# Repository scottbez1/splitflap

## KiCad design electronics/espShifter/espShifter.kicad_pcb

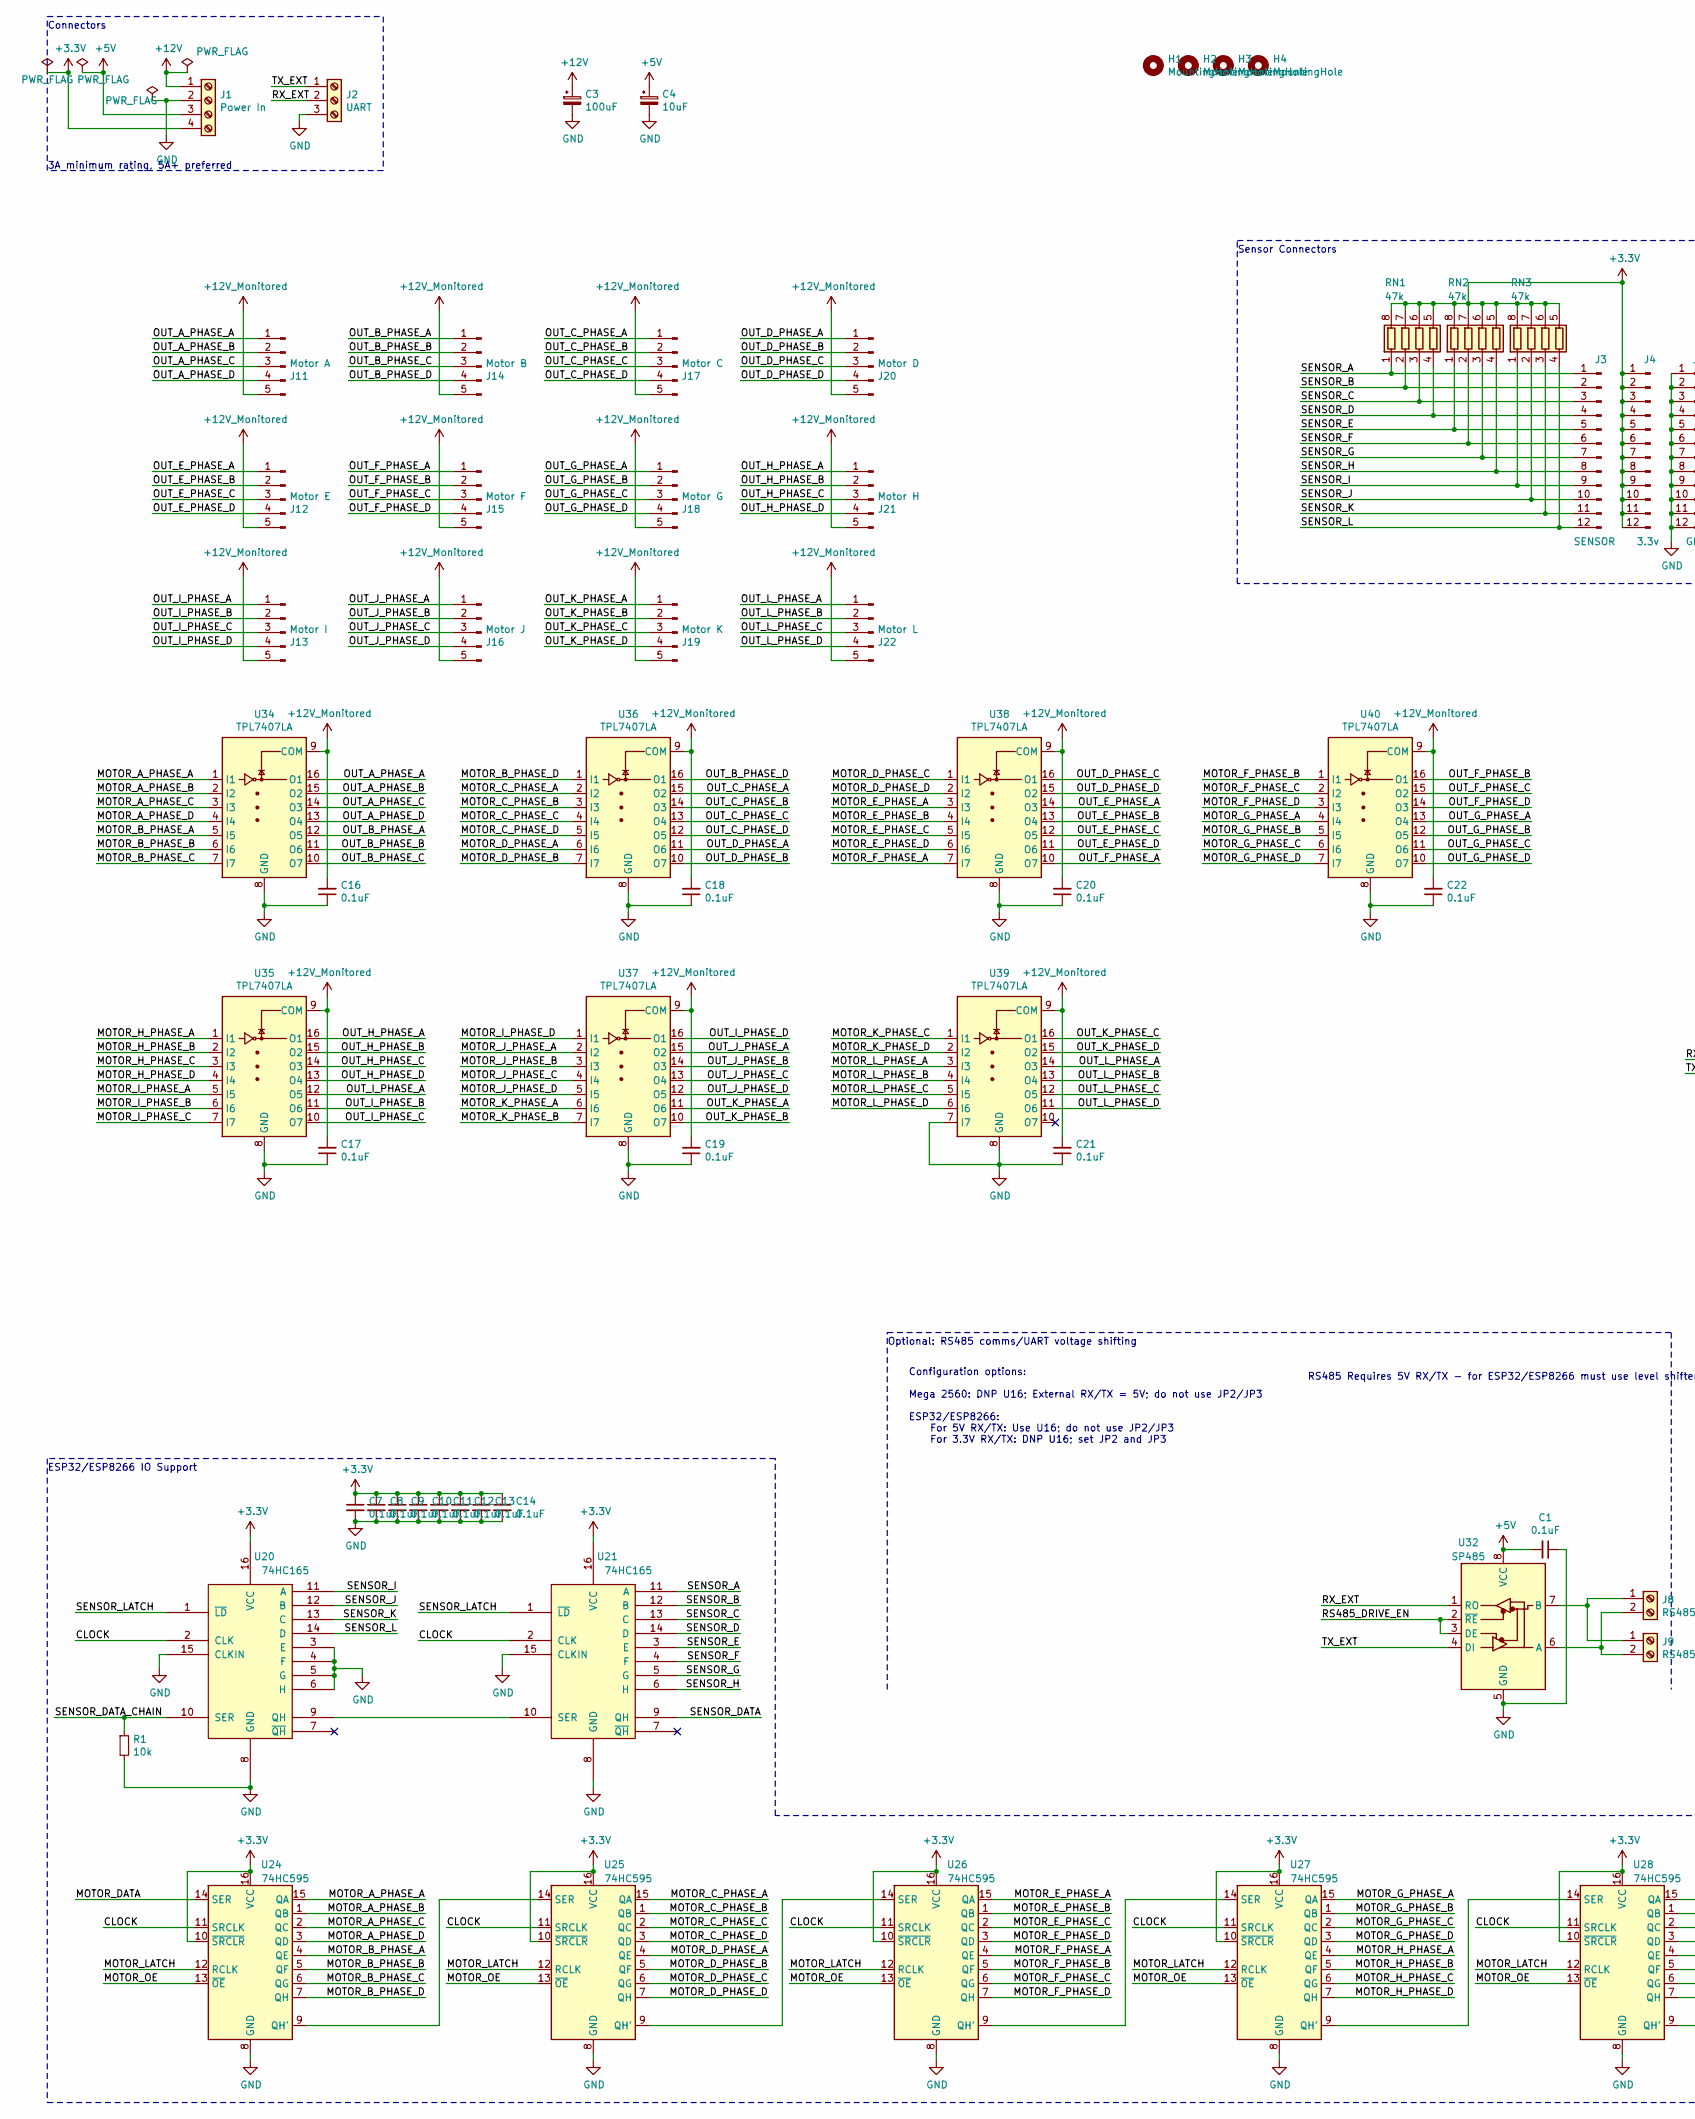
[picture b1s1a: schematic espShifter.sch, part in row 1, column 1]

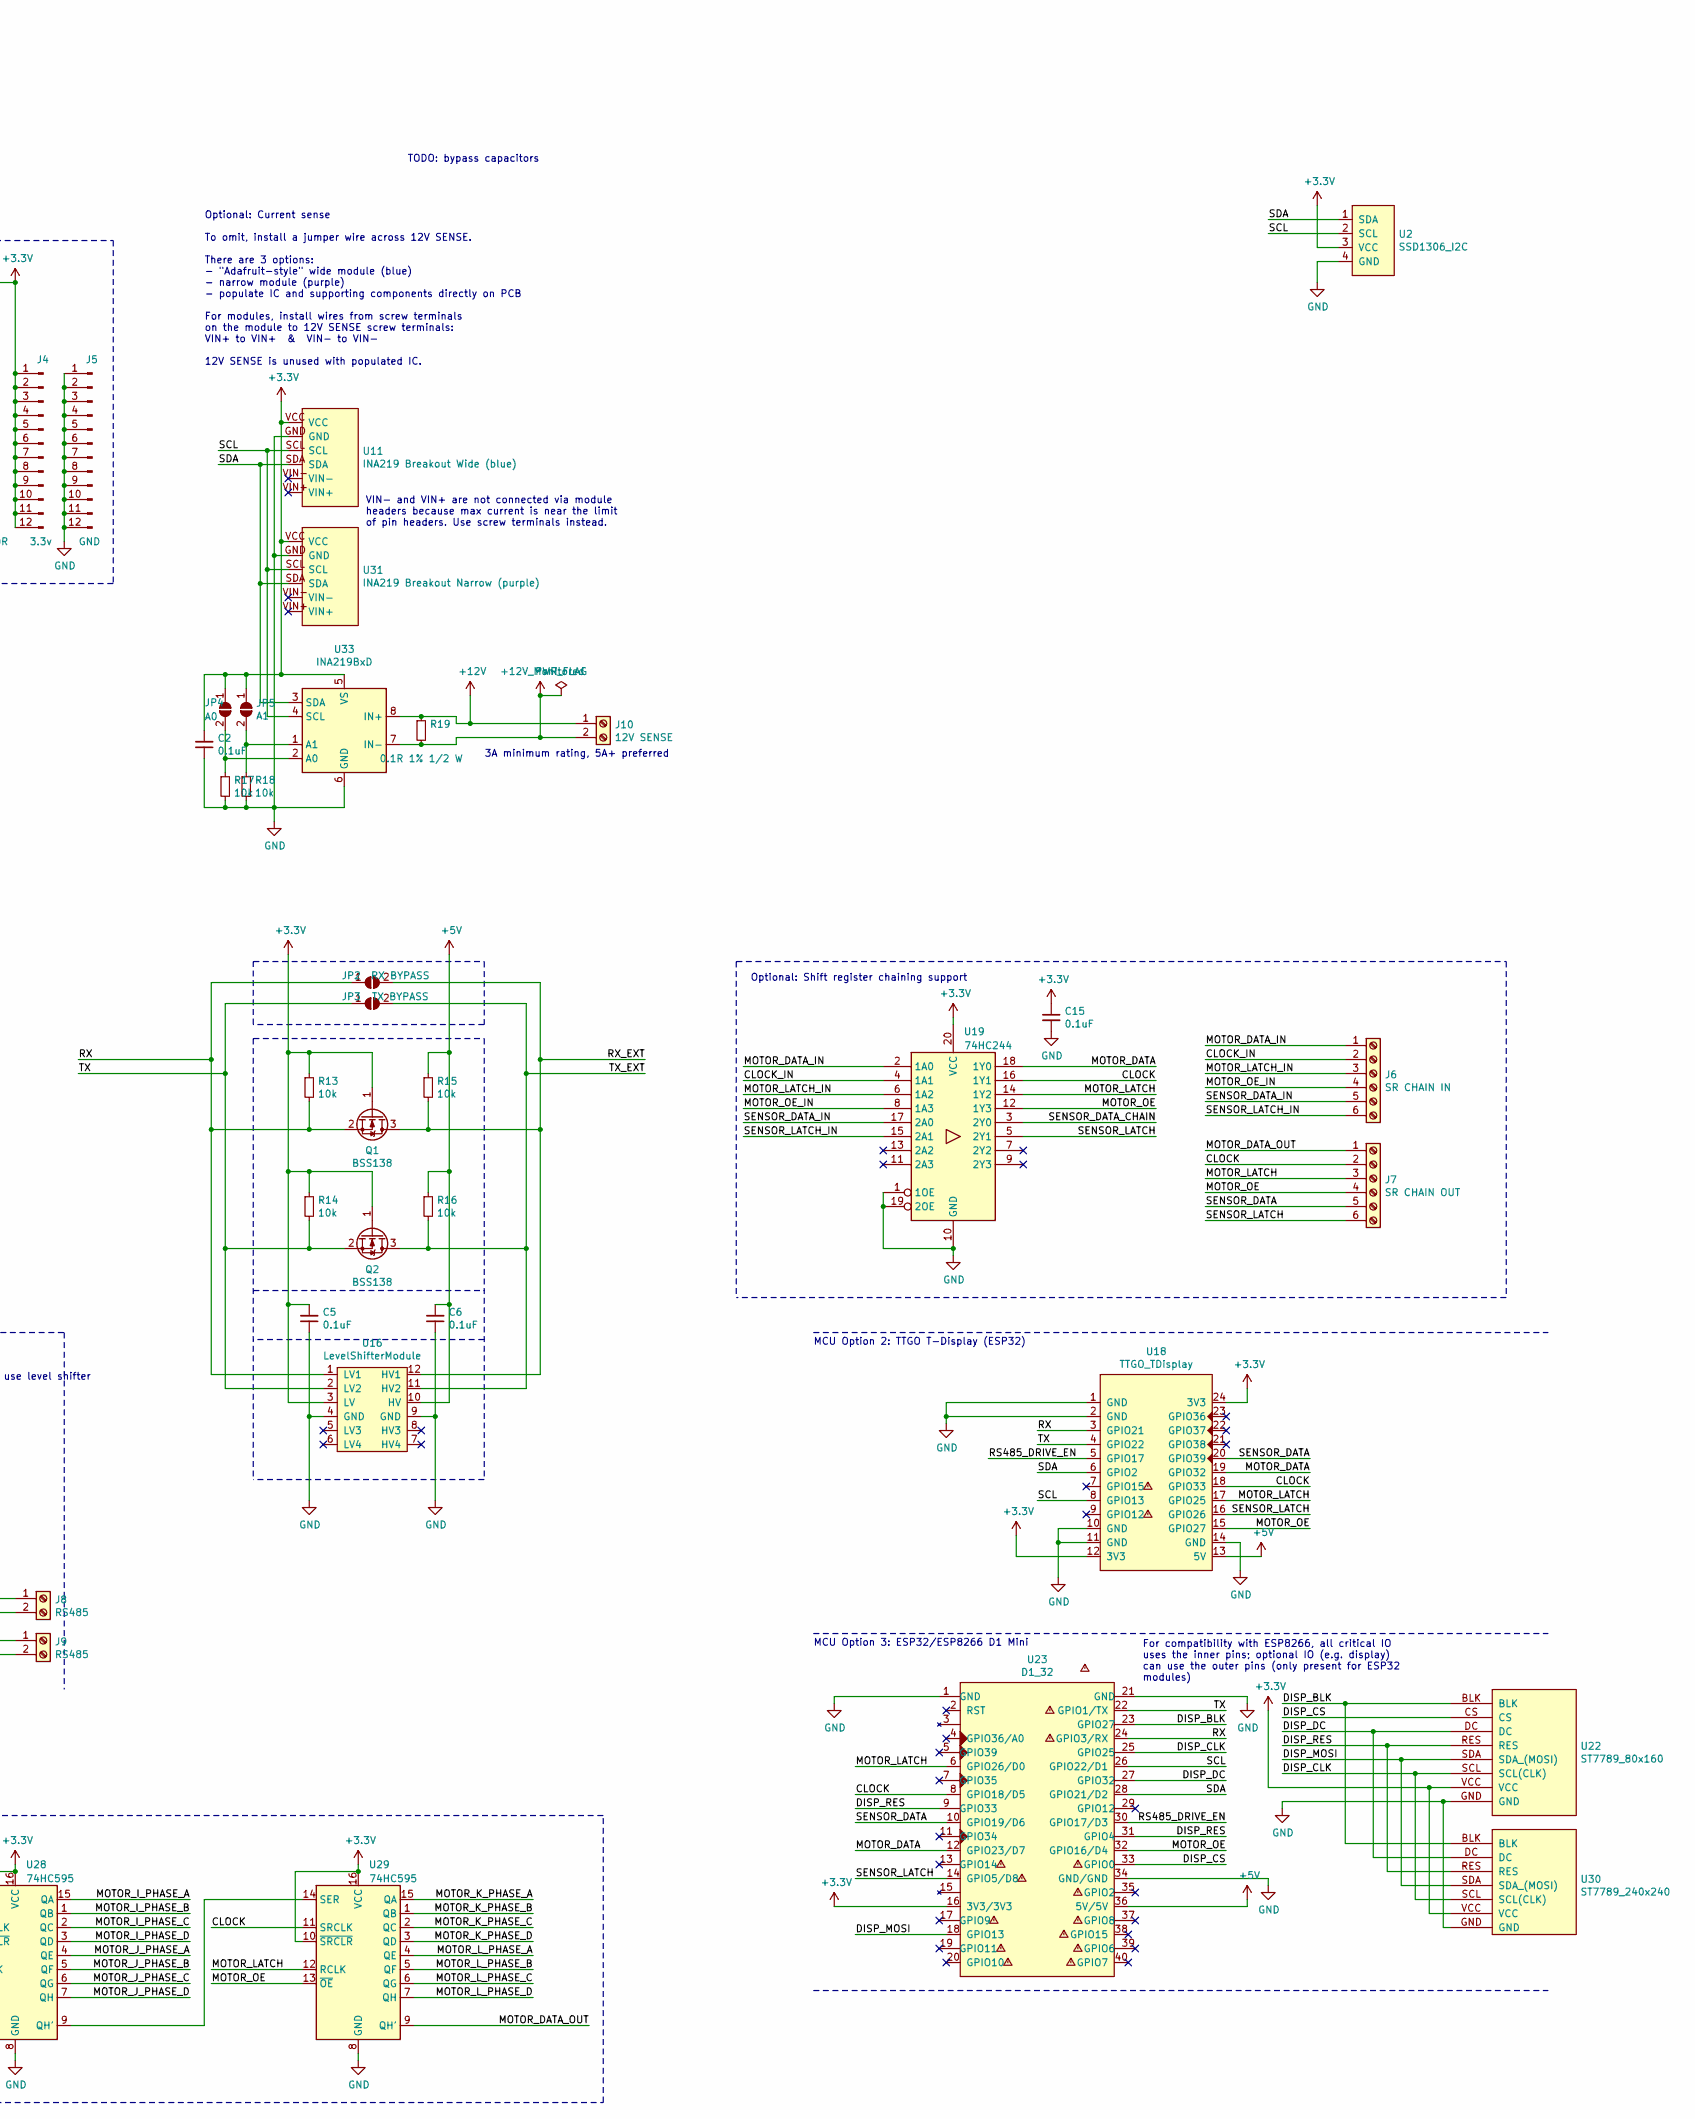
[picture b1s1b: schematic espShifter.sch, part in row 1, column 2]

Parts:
C1, C2, C5, C6, C7, C8, C9, C10, C11, C12, C13, C14, C15, C16, C17, C18, C19, C20, C21, C22: 0.1uF; C_0805_2012Metric
C3: 100uF; CP_Elec_8x10.5
C4: 10uF; CP_Elec_4x5.4
H1, H2, H3, H4: MountingHole; MountingHole_4.3mm_M4_ISO7380_Pad
J1: Power In; TerminalBlock_bornier-4_P5.08mm
J2: UART; TerminalBlock_bornier-3_P5.08mm
J3: SENSOR; PinHeader_1x12_P2.54mm_Vertical
J4: 3.3v; PinHeader_1x12_P2.54mm_Vertical
J5: GND; PinHeader_1x12_P2.54mm_Vertical
J6: SR CHAIN IN; PinSocket_1x06_P2.54mm_Vertical
J7: SR CHAIN OUT; PinSocket_1x06_P2.54mm_Vertical
J8, J9: RS485; TerminalBlock_bornier-2_P5.08mm
J10: 12V SENSE; TerminalBlock_bornier-2_P5.08mm
J11: Motor A; JST_XH_2-5mm_5pin
J12: Motor E; JST_XH_2-5mm_5pin
J13: Motor I; JST_XH_2-5mm_5pin
J14: Motor B; JST_XH_2-5mm_5pin
J15: Motor F; JST_XH_2-5mm_5pin
J16: Motor J; JST_XH_2-5mm_5pin
J17: Motor C; JST_XH_2-5mm_5pin
J18: Motor G; JST_XH_2-5mm_5pin
J19: Motor K; JST_XH_2-5mm_5pin
J20: Motor D; JST_XH_2-5mm_5pin
J21: Motor H; JST_XH_2-5mm_5pin
J22: Motor L; JST_XH_2-5mm_5pin
JP2: RX BYPASS; SolderJumper-2_P1.3mm_Open_TrianglePad1.0x1.5mm
JP3: TX BYPASS; SolderJumper-2_P1.3mm_Open_TrianglePad1.0x1.5mm
JP4: A0; SolderJumper-2_P1.3mm_Open_TrianglePad1.0x1.5mm
JP5: A1; SolderJumper-2_P1.3mm_Open_TrianglePad1.0x1.5mm
Q1, Q2: BSS138; SOT-23
R1, R13, R14, R15, R16, R17, R18: 10k; R_0805_2012Metric
R19: 0.1R 1% 1/2 W; R_2512_6332Metric_Pad1.52x3.35mm_HandSolder
RN1, RN2, RN3: 47k; R_Cat16-4
U2: SSD1306_I2C; PinSocket_1x04_P2.54mm_Vertical
U11: INA219 Breakout Wide (blue); INA219_LARGE
U16: LevelShifterModule
U18: TTGO_TDisplay; T-DISPLAY
U19: 74HC244; TSSOP-20_4.4x6.5mm_P0.65mm
U20, U21: 74HC165; SOIC-16_3.9x9.9mm_P1.27mm
U22: ST7789_80x160
U23: D1_32
U24, U25, U26, U27, U28, U29: 74HC595; SOIC-16_3.9x9.9mm_P1.27mm
U30: ST7789_240x240
U31: INA219 Breakout Narrow (purple); INA219_SMALL
U32: SP485; SOIC-8_3.9x4.9mm_P1.27mm
U33: INA219BxD; SOIC-8_3.9x4.9mm_P1.27mm
U34, U35, U36, U37, U38, U39, U40: TPL7407LA; SOIC-16_3.9x9.9mm_P1.27mm

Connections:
+3V3: C2.2, C5.2, C7.1, C8.1, C9.1, C10.1, C11.1, C12.1, C13.1, C14.1, C15.1, J1.4, J4.1, J4.2, J4.3, J4.4, J4.5, J4.6, J4.7, J4.8, J4.9, J4.10, J4.11, J4.12, JP4.1 (A), JP5.1 (A), Q1.1 (G), Q2.1 (G), R13.1, R14.1, RN1.5 (R4.2), RN1.6 (R3.2), RN1.7 (R2.2), RN1.8 (R1.2), RN2.5 (R4.2), RN2.6 (R3.2), RN2.7 (R2.2), RN2.8 (R1.2), RN3.5 (R4.2), RN3.6 (R3.2), RN3.7 (R2.2), RN3.8 (R1.2), U2.3 (VCC), U11.VCC, U16.3 (LV), U18.12 (3V3), U18.24 (3V3), U19.20 (VCC), U20.16 (VCC), U21.16 (VCC), U22.VCC, U23.16 (3V3/3V3), U24.10 (~SRCLR), U24.16 (VCC), U25.10 (~SRCLR), U25.16 (VCC), U26.10 (~SRCLR), U26.16 (VCC), U27.10 (~SRCLR), U27.16 (VCC), U28.10 (~SRCLR), U28.16 (VCC), U29.10 (~SRCLR), U29.16 (VCC), U30.VCC, U31.VCC, U33.5 (VS)
+5V: C1.2, C4.1, C6.2, J1.3, R15.1, R16.1, U16.10 (HV), U18.13 (5V), U23.36 (5V/5V), U32.8 (VCC)
+12V: C3.1, J1.1, J10.1, R19.1, U33.8 (IN+)
+12V_Monitored: C16.2, C17.2, C18.2, C19.2, C20.2, C21.2, C22.2, J10.2, J11.5, J12.5, J13.5, J14.5, J15.5, J16.5, J17.5, J18.5, J19.5, J20.5, J21.5, J22.5, R19.2, U33.7 (IN-), U34.9 (COM), U35.9 (COM), U36.9 (COM), U37.9 (COM), U38.9 (COM), U39.9 (COM), U40.9 (COM)
/CLOCK: J7.2, U18.18 (GPIO33), U19.16 (1Y1), U20.2 (CLK), U21.2 (CLK), U23.8 (GPIO18/D5), U24.11 (SRCLK), U25.11 (SRCLK), U26.11 (SRCLK), U27.11 (SRCLK), U28.11 (SRCLK), U29.11 (SRCLK)
/CLOCK_IN: J6.2, U19.4 (1A1)
/DISP_BLK: U22.BLK, U23.23 (GPIO27), U30.BLK
/DISP_CLK: U22.SCL (SCL(CLK)), U23.25 (GPIO25), U30.SCL (SCL(CLK))
/DISP_CS: U22.CS, U23.33 (GPIO0)
/DISP_DC: U22.DC, U23.27 (GPIO32), U30.DC
/DISP_MOSI: U22.SDA (SDA_(MOSI)), U23.18 (GPIO13), U30.SDA (SDA_(MOSI))
/DISP_RES: U22.RES, U23.9 (GPIO33), U23.31 (GPIO4), U30.RES
/MOTOR_A_PHASE_A: U24.15 (QA), U34.1 (I1)
/MOTOR_A_PHASE_B: U24.1 (QB), U34.2 (I2)
/MOTOR_A_PHASE_C: U24.2 (QC), U34.3 (I3)
/MOTOR_A_PHASE_D: U24.3 (QD), U34.4 (I4)
/MOTOR_B_PHASE_A: U24.4 (QE), U34.5 (I5)
/MOTOR_B_PHASE_B: U24.5 (QF), U34.6 (I6)
/MOTOR_B_PHASE_C: U24.6 (QG), U34.7 (I7)
/MOTOR_B_PHASE_D: U24.7 (QH), U36.1 (I1)
/MOTOR_C_PHASE_A: U25.15 (QA), U36.2 (I2)
/MOTOR_C_PHASE_B: U25.1 (QB), U36.3 (I3)
/MOTOR_C_PHASE_C: U25.2 (QC), U36.4 (I4)
/MOTOR_C_PHASE_D: U25.3 (QD), U36.5 (I5)
/MOTOR_DATA: U18.19 (GPIO32), U19.18 (1Y0), U23.12 (GPIO23/D7), U24.14 (SER)
/MOTOR_DATA_IN: J6.1, U19.2 (1A0)
/MOTOR_DATA_OUT: J7.1, U29.9 (QH')
/MOTOR_D_PHASE_A: U25.4 (QE), U36.6 (I6)
/MOTOR_D_PHASE_B: U25.5 (QF), U36.7 (I7)
/MOTOR_D_PHASE_C: U25.6 (QG), U38.1 (I1)
/MOTOR_D_PHASE_D: U25.7 (QH), U38.2 (I2)
/MOTOR_E_PHASE_A: U26.15 (QA), U38.3 (I3)
/MOTOR_E_PHASE_B: U26.1 (QB), U38.4 (I4)
/MOTOR_E_PHASE_C: U26.2 (QC), U38.5 (I5)
/MOTOR_E_PHASE_D: U26.3 (QD), U38.6 (I6)
/MOTOR_F_PHASE_A: U26.4 (QE), U38.7 (I7)
/MOTOR_F_PHASE_B: U26.5 (QF), U40.1 (I1)
/MOTOR_F_PHASE_C: U26.6 (QG), U40.2 (I2)
/MOTOR_F_PHASE_D: U26.7 (QH), U40.3 (I3)
/MOTOR_G_PHASE_A: U27.15 (QA), U40.4 (I4)
/MOTOR_G_PHASE_B: U27.1 (QB), U40.5 (I5)
/MOTOR_G_PHASE_C: U27.2 (QC), U40.6 (I6)
/MOTOR_G_PHASE_D: U27.3 (QD), U40.7 (I7)
/MOTOR_H_PHASE_A: U27.4 (QE), U35.1 (I1)
/MOTOR_H_PHASE_B: U27.5 (QF), U35.2 (I2)
/MOTOR_H_PHASE_C: U27.6 (QG), U35.3 (I3)
/MOTOR_H_PHASE_D: U27.7 (QH), U35.4 (I4)
/MOTOR_I_PHASE_A: U28.15 (QA), U35.5 (I5)
/MOTOR_I_PHASE_B: U28.1 (QB), U35.6 (I6)
/MOTOR_I_PHASE_C: U28.2 (QC), U35.7 (I7)
/MOTOR_I_PHASE_D: U28.3 (QD), U37.1 (I1)
/MOTOR_J_PHASE_A: U28.4 (QE), U37.2 (I2)
/MOTOR_J_PHASE_B: U28.5 (QF), U37.3 (I3)
/MOTOR_J_PHASE_C: U28.6 (QG), U37.4 (I4)
/MOTOR_J_PHASE_D: U28.7 (QH), U37.5 (I5)
/MOTOR_K_PHASE_A: U29.15 (QA), U37.6 (I6)
/MOTOR_K_PHASE_B: U29.1 (QB), U37.7 (I7)
/MOTOR_K_PHASE_C: U29.2 (QC), U39.1 (I1)
/MOTOR_K_PHASE_D: U29.3 (QD), U39.2 (I2)
/MOTOR_LATCH: J7.3, U18.17 (GPIO25), U19.14 (1Y2), U23.6 (GPIO26/D0), U24.12 (RCLK), U25.12 (RCLK), U26.12 (RCLK), U27.12 (RCLK), U28.12 (RCLK), U29.12 (RCLK)
/MOTOR_LATCH_IN: J6.3, U19.6 (1A2)
/MOTOR_L_PHASE_A: U29.4 (QE), U39.3 (I3)
/MOTOR_L_PHASE_B: U29.5 (QF), U39.4 (I4)
/MOTOR_L_PHASE_C: U29.6 (QG), U39.5 (I5)
/MOTOR_L_PHASE_D: U29.7 (QH), U39.6 (I6)
/MOTOR_OE: J7.4, U18.15 (GPIO27), U19.12 (1Y3), U23.32 (GPIO16/D4), U24.13 (~OE), U25.13 (~OE), U26.13 (~OE), U27.13 (~OE), U28.13 (~OE), U29.13 (~OE)
/MOTOR_OE_IN: J6.4, U19.8 (1A3)
/OUT_A_PHASE_A: J11.1, U34.16 (O1)
/OUT_A_PHASE_B: J11.2, U34.15 (O2)
/OUT_A_PHASE_C: J11.3, U34.14 (O3)
/OUT_A_PHASE_D: J11.4, U34.13 (O4)
/OUT_B_PHASE_A: J14.1, U34.12 (O5)
/OUT_B_PHASE_B: J14.2, U34.11 (O6)
/OUT_B_PHASE_C: J14.3, U34.10 (O7)
/OUT_B_PHASE_D: J14.4, U36.16 (O1)
/OUT_C_PHASE_A: J17.1, U36.15 (O2)
/OUT_C_PHASE_B: J17.2, U36.14 (O3)
/OUT_C_PHASE_C: J17.3, U36.13 (O4)
/OUT_C_PHASE_D: J17.4, U36.12 (O5)
/OUT_D_PHASE_A: J20.1, U36.11 (O6)
/OUT_D_PHASE_B: J20.2, U36.10 (O7)
/OUT_D_PHASE_C: J20.3, U38.16 (O1)
/OUT_D_PHASE_D: J20.4, U38.15 (O2)
/OUT_E_PHASE_A: J12.1, U38.14 (O3)
/OUT_E_PHASE_B: J12.2, U38.13 (O4)
/OUT_E_PHASE_C: J12.3, U38.12 (O5)
/OUT_E_PHASE_D: J12.4, U38.11 (O6)
/OUT_F_PHASE_A: J15.1, U38.10 (O7)
/OUT_F_PHASE_B: J15.2, U40.16 (O1)
/OUT_F_PHASE_C: J15.3, U40.15 (O2)
/OUT_F_PHASE_D: J15.4, U40.14 (O3)
/OUT_G_PHASE_A: J18.1, U40.13 (O4)
/OUT_G_PHASE_B: J18.2, U40.12 (O5)
/OUT_G_PHASE_C: J18.3, U40.11 (O6)
/OUT_G_PHASE_D: J18.4, U40.10 (O7)
/OUT_H_PHASE_A: J21.1, U35.16 (O1)
/OUT_H_PHASE_B: J21.2, U35.15 (O2)
/OUT_H_PHASE_C: J21.3, U35.14 (O3)
/OUT_H_PHASE_D: J21.4, U35.13 (O4)
/OUT_I_PHASE_A: J13.1, U35.12 (O5)
/OUT_I_PHASE_B: J13.2, U35.11 (O6)
/OUT_I_PHASE_C: J13.3, U35.10 (O7)
/OUT_I_PHASE_D: J13.4, U37.16 (O1)
/OUT_J_PHASE_A: J16.1, U37.15 (O2)
/OUT_J_PHASE_B: J16.2, U37.14 (O3)
/OUT_J_PHASE_C: J16.3, U37.13 (O4)
/OUT_J_PHASE_D: J16.4, U37.12 (O5)
/OUT_K_PHASE_A: J19.1, U37.11 (O6)
/OUT_K_PHASE_B: J19.2, U37.10 (O7)
/OUT_K_PHASE_C: J19.3, U39.16 (O1)
/OUT_K_PHASE_D: J19.4, U39.15 (O2)
/OUT_L_PHASE_A: J22.1, U39.14 (O3)
/OUT_L_PHASE_B: J22.2, U39.13 (O4)
/OUT_L_PHASE_C: J22.3, U39.12 (O5)
/OUT_L_PHASE_D: J22.4, U39.11 (O6)
/RS485_DRIVE_EN: U18.5 (GPIO17), U23.30 (GPIO17/D3), U32.2 (~RE), U32.3 (DE)
/RX: JP2.1 (A), Q1.2 (S), R13.2, U16.1 (LV1), U18.3 (GPIO21), U23.24 (GPIO3/RX)
/RX_EXT: J2.2, JP2.2 (B), Q1.3 (D), R15.2, U16.12 (HV1), U32.1 (RO)
/SCL: U2.2 (SCL), U11.SCL, U18.8 (GPIO13), U23.26 (GPIO22/D1), U31.SCL, U33.4 (SCL)
/SDA: U2.1 (SDA), U11.SDA, U18.6 (GPIO2), U23.28 (GPIO21/D2), U31.SDA, U33.3 (SDA)
/SENSOR_A: J3.1, RN1.1 (R1.1), U21.11 (A)
/SENSOR_B: J3.2, RN1.2 (R2.1), U21.12 (B)
/SENSOR_C: J3.3, RN1.3 (R3.1), U21.13 (C)
/SENSOR_D: J3.4, RN1.4 (R4.1), U21.14 (D)
/SENSOR_DATA: J7.5, U18.20 (GPIO39), U21.9 (QH), U23.10 (GPIO19/D6)
/SENSOR_DATA_CHAIN: R1.1, U19.3 (2Y0), U20.10 (SER)
/SENSOR_DATA_IN: J6.5, U19.17 (2A0)
/SENSOR_E: J3.5, RN2.1 (R1.1), U21.3 (E)
/SENSOR_F: J3.6, RN2.2 (R2.1), U21.4 (F)
/SENSOR_G: J3.7, RN2.3 (R3.1), U21.5 (G)
/SENSOR_H: J3.8, RN2.4 (R4.1), U21.6 (H)
/SENSOR_I: J3.9, RN3.1 (R1.1), U20.11 (A)
/SENSOR_J: J3.10, RN3.2 (R2.1), U20.12 (B)
/SENSOR_K: J3.11, RN3.3 (R3.1), U20.13 (C)
/SENSOR_L: J3.12, RN3.4 (R4.1), U20.14 (D)
/SENSOR_LATCH: J7.6, U18.16 (GPIO26), U19.5 (2Y1), U20.1 (~LD), U21.1 (~LD), U23.14 (GPIO5/D8)
/SENSOR_LATCH_IN: J6.6, U19.15 (2A1)
/TX: JP3.1 (A), Q2.2 (S), R14.2, U16.2 (LV2), U18.4 (GPIO22), U23.22 (GPIO1/TX)
/TX_EXT: J2.1, JP3.2 (B), Q2.3 (D), R16.2, U16.11 (HV2), U32.4 (DI)
GND: C1.1, C2.1, C3.2, C4.2, C5.1, C6.1, C7.2, C8.2, C9.2, C10.2, C11.2, C12.2, C13.2, C14.2, C15.2, C16.1, C17.1, C18.1, C19.1, C20.1, C21.1, C22.1, J1.2, J2.3, J5.1, J5.2, J5.3, J5.4, J5.5, J5.6, J5.7, J5.8, J5.9, J5.10, J5.11, J5.12, R1.2, R17.2, R18.2, U2.4 (GND), U11.GND, U16.4 (GND), U16.9 (GND), U18.1 (GND), U18.2 (GND), U18.10 (GND), U18.11 (GND), U18.14 (GND), U19.1 (1OE), U19.10 (GND), U19.19 (2OE), U20.3 (E), U20.4 (F), U20.5 (G), U20.6 (H), U20.8 (GND), U20.15 (CLKIN), U21.8 (GND), U21.15 (CLKIN), U22.GND, U23.1 (GND), U23.21 (GND), U23.34 (GND/GND), U24.8 (GND), U25.8 (GND), U26.8 (GND), U27.8 (GND), U28.8 (GND), U29.8 (GND), U30.GND, U31.GND, U32.5 (GND), U33.6 (GND), U34.8 (GND), U35.8 (GND), U36.8 (GND), U37.8 (GND), U38.8 (GND), U39.7 (I7), U39.8 (GND), U40.8 (GND)
unnamed: J8.1, J9.1, U32.7 (B)
unnamed: J8.2, J9.2, U32.6 (A)
unnamed: JP4.2 (B), R17.1, U33.2 (A0)
unnamed: JP5.2 (B), R18.1, U33.1 (A1)
unnamed: U20.9 (QH), U21.10 (SER)
unnamed: U24.9 (QH'), U25.14 (SER)
unnamed: U25.9 (QH'), U26.14 (SER)
unnamed: U26.9 (QH'), U27.14 (SER)
unnamed: U27.9 (QH'), U28.14 (SER)
unnamed: U28.9 (QH'), U29.14 (SER)

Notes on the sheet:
Optional: Shift register chaining support
MCU Option 2: TTGO T-Display (ESP32)
MCU Option 3: ESP32/ESP8266 D1 Mini
Optional: RS485 comms/UART voltage shifting
ESP32/ESP8266 IO Support
Sensor Connectors
Optional: Current sense To omit, install a jumper wire across 12V SENSE. There are 3 options: - "Adafruit-style" wide module (blue) - narrow module (purple) - populate IC and supporting components directly on PCB For modules, install wires from screw terminals on the module to 12V SENSE screw termi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
Connectors
For compatibility with ESP8266, all critical IO uses the inner pins; optional IO (e.g. display) can use the outer pins (only present for ESP32 modules)
Configuration options: Mega 2560: DNP U16; External RX/TX = 5V; do not use JP2/JP3 ESP32/ESP8266: For 5V RX/TX: Use U16; do not use JP2/JP3 For 3.3V RX/TX: DNP U16; set JP2 and JP3
RS485 Requires 5V RX/TX - for ESP32/ESP8266 must use level shifter
VIN- and VIN+ are not connected via module headers because max current is near the limit of pin headers. Use screw terminals instead.
3A minimum rating, 5A+ preferred
TODO: bypass capacitors

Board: 2 copper layers, 91 parts (0 on the bottom side), 150 nets, no tracks yet.
